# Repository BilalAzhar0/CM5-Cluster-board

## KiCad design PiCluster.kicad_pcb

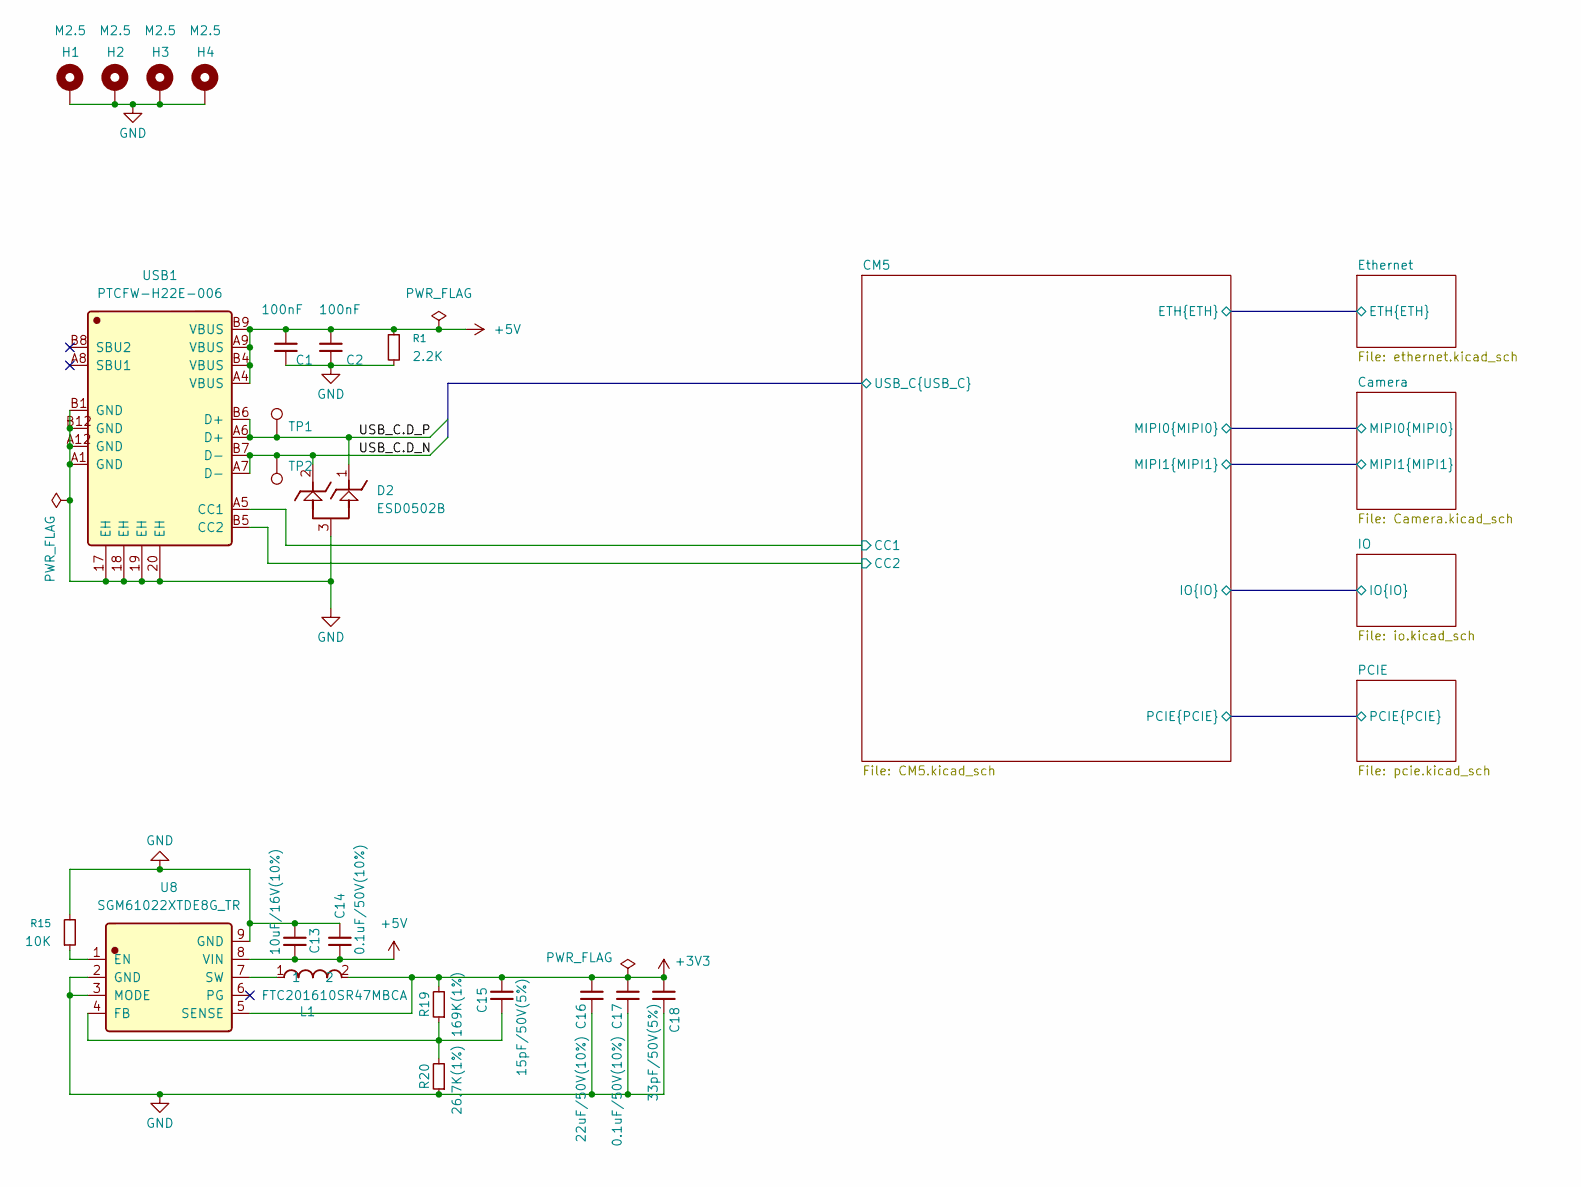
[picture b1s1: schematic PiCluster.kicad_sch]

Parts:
C1, C2: 100nF; C_0402_1005Metric
C13: 10uF/16V(10%); C_0603_1608Metric
C14, C17: 0.1uF/50V(10%); C_0402_1005Metric
C15: 15pF/50V(5%); C_0402_1005Metric
C16: 22uF/50V(10%); C_0603_1608Metric
C18: 33pF/50V(5%); C_0402_1005Metric
D2: ESD0502B; Manufacturer Part ESD0502B-HXY; LCSC C4748781
H1, H2, H3, H4: M2.5; MountingHole_2.5mm_Pad_TopBottom
L1: FTC201610SR47MBCA; Manufacturer Part FTC201610SR47MBCA; LCSC C5832340
R1: 2.2K; R_0402_1005Metric
R15: 10K; R_0402_1005Metric
R19: 169K(1%); R_0402_1005Metric
R20: 26.7K(1%); R_0402_1005Metric
TP1, TP2: TestPoint; TestPoint_Pad_D1.0mm
U8: SGM61022XTDE8G_TR; Manufacturer Part SGM61022XTDE8G/TR; LCSC C5153652
USB1: PTCFW-H22E-006; Manufacturer Part PTCFW-H22E-006; LCSC C54829830

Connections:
+3V3: C15.2, C16.2, C17.2, C18.2, L1.2, R19.2, U8.5 (SENSE); also elsewhere on the board
+5V: C1.1, C2.1, C13.1, C14.2, R1.1, U8.8 (VIN), USB1.A4 (VBUS), USB1.A9 (VBUS), USB1.B4 (VBUS), USB1.B9 (VBUS); also elsewhere on the board
/CM5/CC1: USB1.A5 (CC1); also elsewhere on the board
/CM5/CC2: USB1.B5 (CC2); also elsewhere on the board
/CM5/USB_C.D_N: D2.2, TP2.1 (1_1), USB1.A7 (D-), USB1.B7 (D-); also elsewhere on the board
/CM5/USB_C.D_P: D2.1, TP1.1 (1_1), USB1.A6 (D+), USB1.B6 (D+); also elsewhere on the board
GND: C1.2, C2.2, C13.2, C14.1, C16.1, C17.1, C18.1, D2.3, H1.1 (1_1), H2.1 (1_1), H3.1 (1_1), H4.1 (1_1), R1.2, R15.2, R20.1, U8.2 (GND), U8.3 (MODE), U8.9 (GND), USB1.17 (EH), USB1.18 (EH), USB1.19 (EH), USB1.20 (EH), USB1.A1 (GND), USB1.A12 (GND), USB1.B1 (GND), USB1.B12 (GND); also elsewhere on the board
unnamed: R15.1, U8.1 (EN)
unnamed: C15.1, R19.1, R20.2, U8.4 (FB)
unnamed: L1.1, U8.7 (SW)

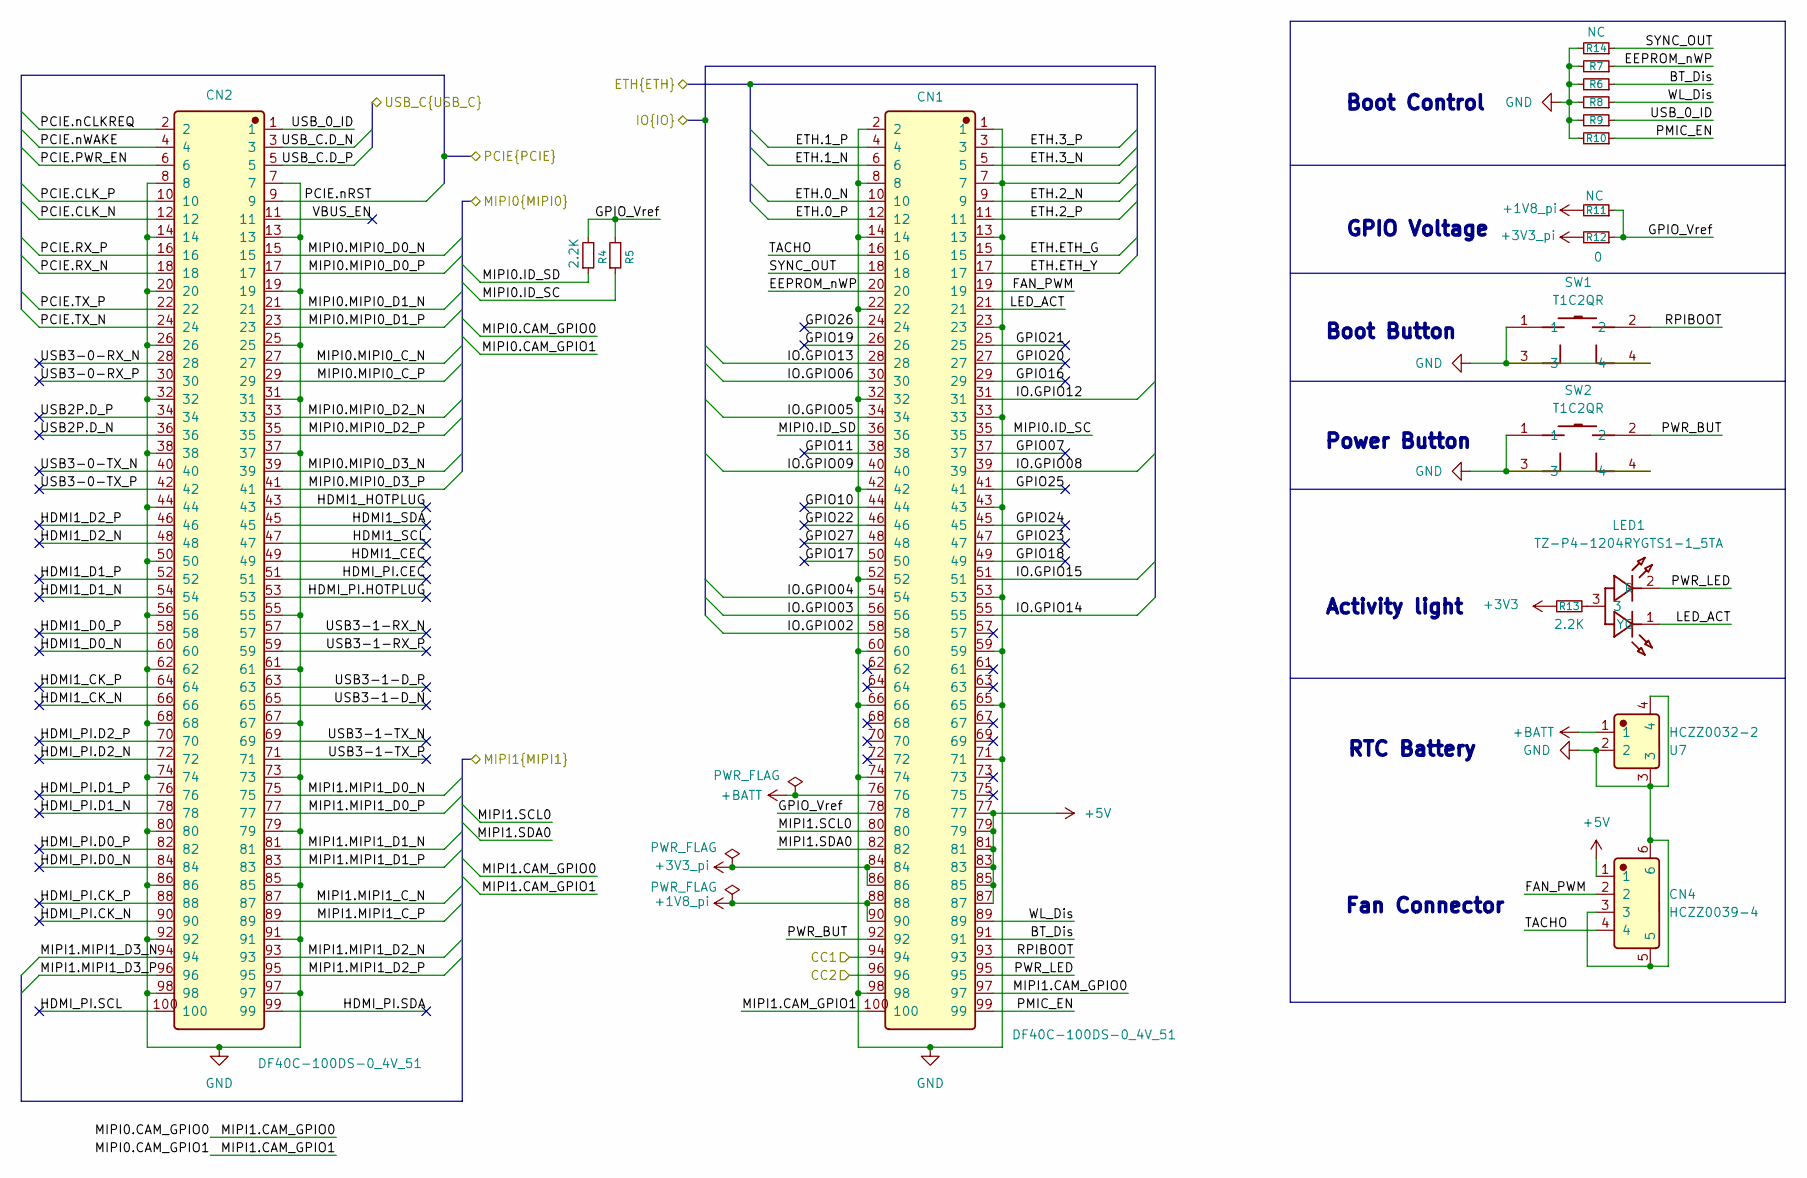
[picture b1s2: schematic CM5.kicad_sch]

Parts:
CN1, CN2: DF40C-100DS-0_4V_51; Manufacturer Part DF40C-100DS-0.4V(51); LCSC C597931
CN4: HCZZ0039-4; Manufacturer Part HCZZ0039-4; LCSC C7433440
LED1: TZ-P4-1204RYGTS1-1_5TA; Manufacturer Part TZ-P4-1204RYGTS1-1.5TA; LCSC C916079
R4, R5, R13: 2.2K; R_0402_1005Metric
R6, R7, R8, R9, R10, R11, R14: NC; R_0402_1005Metric
R12: 0; R_0402_1005Metric
SW1, SW2: T1C2QR; Manufacturer Part T1C2QR; LCSC C495948
U7: HCZZ0032-2; Manufacturer Part HCZZ0032-2; LCSC C7433423

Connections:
+1V8_pi: CN1.88, CN1.90, R11.2
+3V3: R13.1; also elsewhere on the board
+3V3_pi: CN1.84, CN1.86, R12.2
+5V: CN1.77, CN1.79, CN1.81, CN1.83, CN1.85, CN1.87, CN4.1; also elsewhere on the board
+BATT: CN1.76, U7.1
/CM5/BT_Dis: CN1.91, R6.1
/CM5/CC1: CN1.94; also elsewhere on the board
/CM5/CC2: CN1.96; also elsewhere on the board
/CM5/EEPROM_nWP: CN1.20, R7.1
/CM5/ETH.0_N: CN1.10; also elsewhere on the board
/CM5/ETH.0_P: CN1.12; also elsewhere on the board
/CM5/ETH.1_N: CN1.6; also elsewhere on the board
/CM5/ETH.1_P: CN1.4; also elsewhere on the board
/CM5/ETH.2_N: CN1.9; also elsewhere on the board
/CM5/ETH.2_P: CN1.11; also elsewhere on the board
/CM5/ETH.3_N: CN1.5; also elsewhere on the board
/CM5/ETH.3_P: CN1.3; also elsewhere on the board
/CM5/ETH.ETH_G: CN1.15; also elsewhere on the board
/CM5/ETH.ETH_Y: CN1.17; also elsewhere on the board
/CM5/FAN_PWM: CN1.19, CN4.2
/CM5/GPIO07: CN1.37
/CM5/GPIO10: CN1.44
/CM5/GPIO11: CN1.38
/CM5/GPIO16: CN1.29
/CM5/GPIO17: CN1.50
/CM5/GPIO18: CN1.49
/CM5/GPIO19: CN1.26
/CM5/GPIO20: CN1.27
/CM5/GPIO21: CN1.25
/CM5/GPIO22: CN1.46
/CM5/GPIO23: CN1.47
/CM5/GPIO24: CN1.45
/CM5/GPIO25: CN1.41
/CM5/GPIO26: CN1.24
/CM5/GPIO27: CN1.48
/CM5/GPIO_Vref: CN1.78, R4.2, R5.2, R11.1, R12.1
/CM5/HDMI1_CEC: CN2.49
/CM5/HDMI1_CK_N: CN2.66
/CM5/HDMI1_CK_P: CN2.64
/CM5/HDMI1_D0_N: CN2.60
/CM5/HDMI1_D0_P: CN2.58
/CM5/HDMI1_D1_N: CN2.54
/CM5/HDMI1_D1_P: CN2.52
/CM5/HDMI1_D2_N: CN2.48
/CM5/HDMI1_D2_P: CN2.46
/CM5/HDMI1_HOTPLUG: CN2.43
/CM5/HDMI1_SCL: CN2.47
/CM5/HDMI1_SDA: CN2.45
/CM5/HDMI_PI.CEC: CN2.51
/CM5/HDMI_PI.CK_N: CN2.90
/CM5/HDMI_PI.CK_P: CN2.88
/CM5/HDMI_PI.D0_N: CN2.84
/CM5/HDMI_PI.D0_P: CN2.82
/CM5/HDMI_PI.D1_N: CN2.78
/CM5/HDMI_PI.D1_P: CN2.76
/CM5/HDMI_PI.D2_N: CN2.72
/CM5/HDMI_PI.D2_P: CN2.70
/CM5/HDMI_PI.HOTPLUG: CN2.53
/CM5/HDMI_PI.SCL: CN2.100
/CM5/HDMI_PI.SDA: CN2.99
/CM5/IO.GPIO02: CN1.58; also elsewhere on the board
/CM5/IO.GPIO03: CN1.56; also elsewhere on the board
/CM5/IO.GPIO04: CN1.54; also elsewhere on the board
/CM5/IO.GPIO05: CN1.34; also elsewhere on the board
/CM5/IO.GPIO06: CN1.30; also elsewhere on the board
/CM5/IO.GPIO08: CN1.39; also elsewhere on the board
/CM5/IO.GPIO09: CN1.40; also elsewhere on the board
/CM5/IO.GPIO12: CN1.31; also elsewhere on the board
/CM5/IO.GPIO13: CN1.28; also elsewhere on the board
/CM5/IO.GPIO14: CN1.55; also elsewhere on the board
/CM5/IO.GPIO15: CN1.51; also elsewhere on the board
/CM5/LED_ACT: CN1.21, LED1.1 (YG)
/CM5/MIPI0.ID_SC: CN1.35, R5.1; also elsewhere on the board
/CM5/MIPI0.ID_SD: CN1.36, R4.1; also elsewhere on the board
/CM5/MIPI0.MIPI0_C_N: CN2.27; also elsewhere on the board
/CM5/MIPI0.MIPI0_C_P: CN2.29; also elsewhere on the board
/CM5/MIPI0.MIPI0_D0_N: CN2.15; also elsewhere on the board
/CM5/MIPI0.MIPI0_D0_P: CN2.17; also elsewhere on the board
/CM5/MIPI0.MIPI0_D1_N: CN2.21; also elsewhere on the board
/CM5/MIPI0.MIPI0_D1_P: CN2.23; also elsewhere on the board
/CM5/MIPI0.MIPI0_D2_N: CN2.33; also elsewhere on the board
/CM5/MIPI0.MIPI0_D2_P: CN2.35; also elsewhere on the board
/CM5/MIPI0.MIPI0_D3_N: CN2.39; also elsewhere on the board
/CM5/MIPI0.MIPI0_D3_P: CN2.41; also elsewhere on the board
/CM5/MIPI1.CAM_GPIO0: CN1.97; also elsewhere on the board
/CM5/MIPI1.CAM_GPIO1: CN1.100; also elsewhere on the board
/CM5/MIPI1.MIPI1_C_N: CN2.87; also elsewhere on the board
/CM5/MIPI1.MIPI1_C_P: CN2.89; also elsewhere on the board
/CM5/MIPI1.MIPI1_D0_N: CN2.75; also elsewhere on the board
/CM5/MIPI1.MIPI1_D0_P: CN2.77; also elsewhere on the board
/CM5/MIPI1.MIPI1_D1_N: CN2.81; also elsewhere on the board
/CM5/MIPI1.MIPI1_D1_P: CN2.83; also elsewhere on the board
/CM5/MIPI1.MIPI1_D2_N: CN2.93; also elsewhere on the board
/CM5/MIPI1.MIPI1_D2_P: CN2.95; also elsewhere on the board
/CM5/MIPI1.MIPI1_D3_N: CN2.94; also elsewhere on the board
/CM5/MIPI1.MIPI1_D3_P: CN2.96; also elsewhere on the board
/CM5/MIPI1.SCL0: CN1.80; also elsewhere on the board
/CM5/MIPI1.SDA0: CN1.82; also elsewhere on the board
/CM5/PCIE.CLK_N: CN2.12; also elsewhere on the board
/CM5/PCIE.CLK_P: CN2.10; also elsewhere on the board
/CM5/PCIE.PWR_EN: CN2.6; also elsewhere on the board
/CM5/PCIE.RX_N: CN2.18; also elsewhere on the board
/CM5/PCIE.RX_P: CN2.16; also elsewhere on the board
/CM5/PCIE.TX_N: CN2.24; also elsewhere on the board
/CM5/PCIE.TX_P: CN2.22; also elsewhere on the board
/CM5/PCIE.nCLKREQ: CN2.2; also elsewhere on the board
/CM5/PCIE.nRST: CN2.9; also elsewhere on the board
/CM5/PCIE.nWAKE: CN2.4; also elsewhere on the board
/CM5/PMIC_EN: CN1.99, R10.1
/CM5/PWR_BUT: CN1.92, SW2.2
/CM5/PWR_LED: CN1.95, LED1.2 (R)
/CM5/RPIBOOT: CN1.93, SW1.2
/CM5/SYNC_OUT: CN1.18, R14.1
/CM5/TACHO: CN1.16, CN4.4
/CM5/USB2P.D_N: CN2.36
/CM5/USB2P.D_P: CN2.34
/CM5/USB3-0-RX_N: CN2.28
/CM5/USB3-0-RX_P: CN2.30
/CM5/USB3-0-TX_N: CN2.40
/CM5/USB3-0-TX_P: CN2.42
/CM5/USB3-1-D_N: CN2.65
/CM5/USB3-1-D_P: CN2.63
/CM5/USB3-1-RX_N: CN2.57
/CM5/USB3-1-RX_P: CN2.59
/CM5/USB3-1-TX_N: CN2.69
/CM5/USB3-1-TX_P: CN2.71
/CM5/USB_0_ID: CN2.1, R9.1
/CM5/USB_C.D_N: CN2.3; also elsewhere on the board
/CM5/USB_C.D_P: CN2.5; also elsewhere on the board
/CM5/VBUS_EN: CN2.11
/CM5/WL_Dis: CN1.89, R8.1
GND: CN1.1, CN1.2, CN1.7, CN1.8, CN1.13, CN1.14, CN1.22, CN1.23, CN1.32, CN1.33, CN1.42, CN1.43, CN1.52, CN1.53, CN1.59, CN1.60, CN1.65, CN1.66, CN1.71, CN1.74, CN1.98, CN2.7, CN2.8, CN2.13, CN2.14, CN2.19, CN2.20, CN2.25, CN2.26, CN2.31, CN2.32, CN2.37, CN2.38, CN2.44, CN2.50, CN2.55, CN2.56, CN2.61, CN2.62, CN2.67, CN2.68, CN2.73, CN2.74, CN2.79, CN2.80, CN2.85, CN2.86, CN2.91, CN2.92, CN2.97, CN2.98, CN4.3, CN4.5, CN4.6, R6.2, R7.2, R8.2, R9.2, R10.2, R14.2, SW1.1, SW1.3, SW1.4, SW2.1, SW2.3, SW2.4, U7.2, U7.3, U7.4; also elsewhere on the board
unnamed: LED1.3, R13.2

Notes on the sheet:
RTC Battery
Boot Control
GPIO Voltage
Power Button
Activity light
Boot Button
Fan Connector

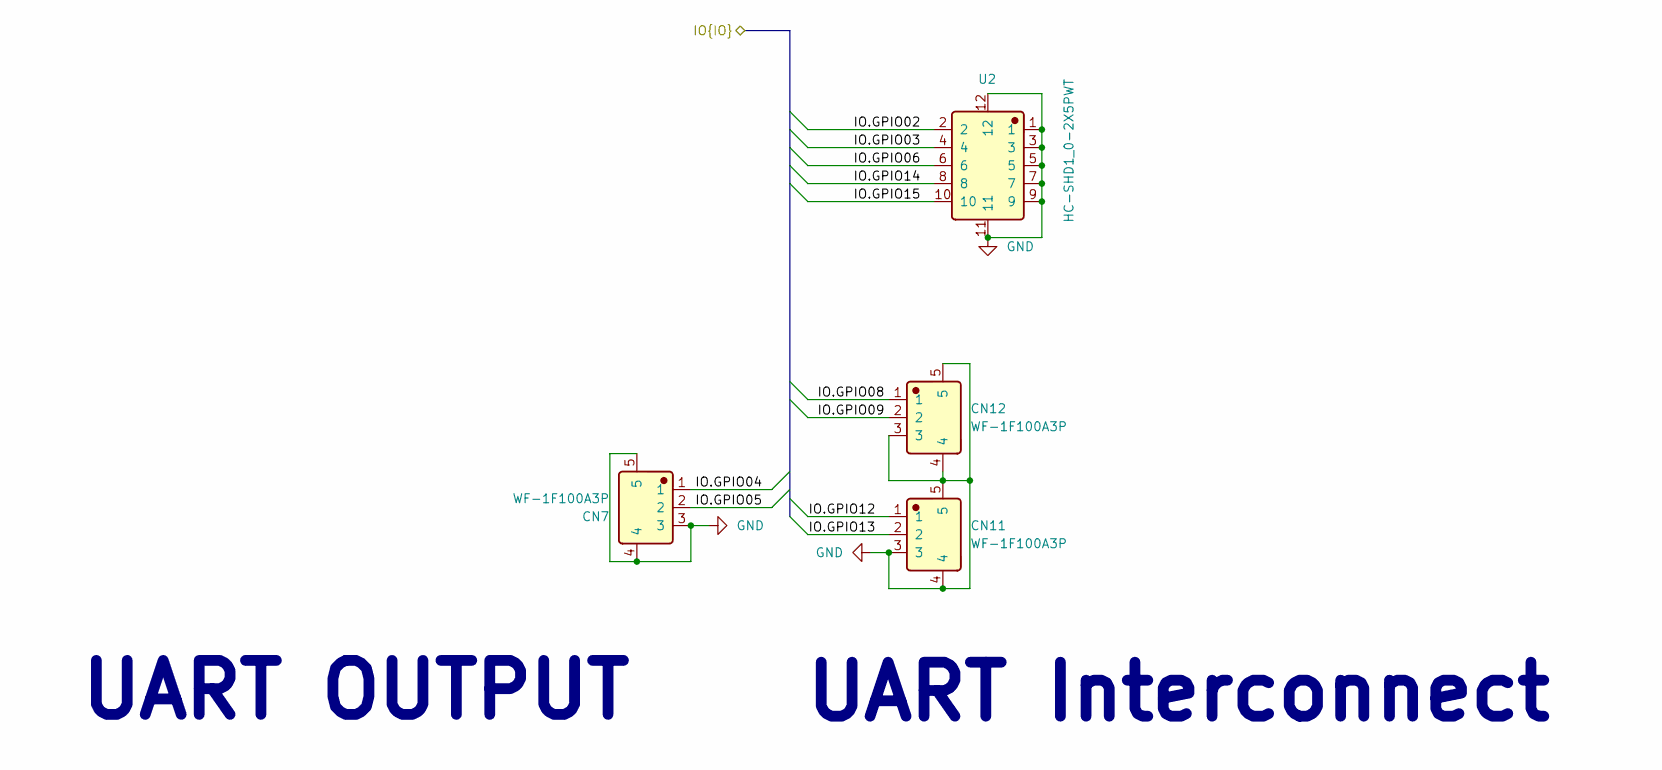
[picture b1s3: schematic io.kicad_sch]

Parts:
CN7, CN11, CN12: WF-1F100A3P; Manufacturer Part WF-1F100A3P; LCSC C23390336
U2: HC-SHD1_0-2X5PWT; Manufacturer Part HC-SHD1.0-2x5PWT; LCSC C19273832

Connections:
/CM5/IO.GPIO02: U2.2; also elsewhere on the board
/CM5/IO.GPIO03: U2.4; also elsewhere on the board
/CM5/IO.GPIO04: CN7.1; also elsewhere on the board
/CM5/IO.GPIO05: CN7.2; also elsewhere on the board
/CM5/IO.GPIO06: U2.6; also elsewhere on the board
/CM5/IO.GPIO08: CN12.1; also elsewhere on the board
/CM5/IO.GPIO09: CN12.2; also elsewhere on the board
/CM5/IO.GPIO12: CN11.1; also elsewhere on the board
/CM5/IO.GPIO13: CN11.2; also elsewhere on the board
/CM5/IO.GPIO14: U2.8; also elsewhere on the board
/CM5/IO.GPIO15: U2.10; also elsewhere on the board
GND: CN7.3, CN7.4, CN7.5, CN11.3, CN11.4, CN11.5, CN12.3, CN12.4, CN12.5, U2.1, U2.3, U2.5, U2.7, U2.9, U2.11, U2.12; also elsewhere on the board

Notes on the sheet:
UART OUTPUT
UART Interconnect

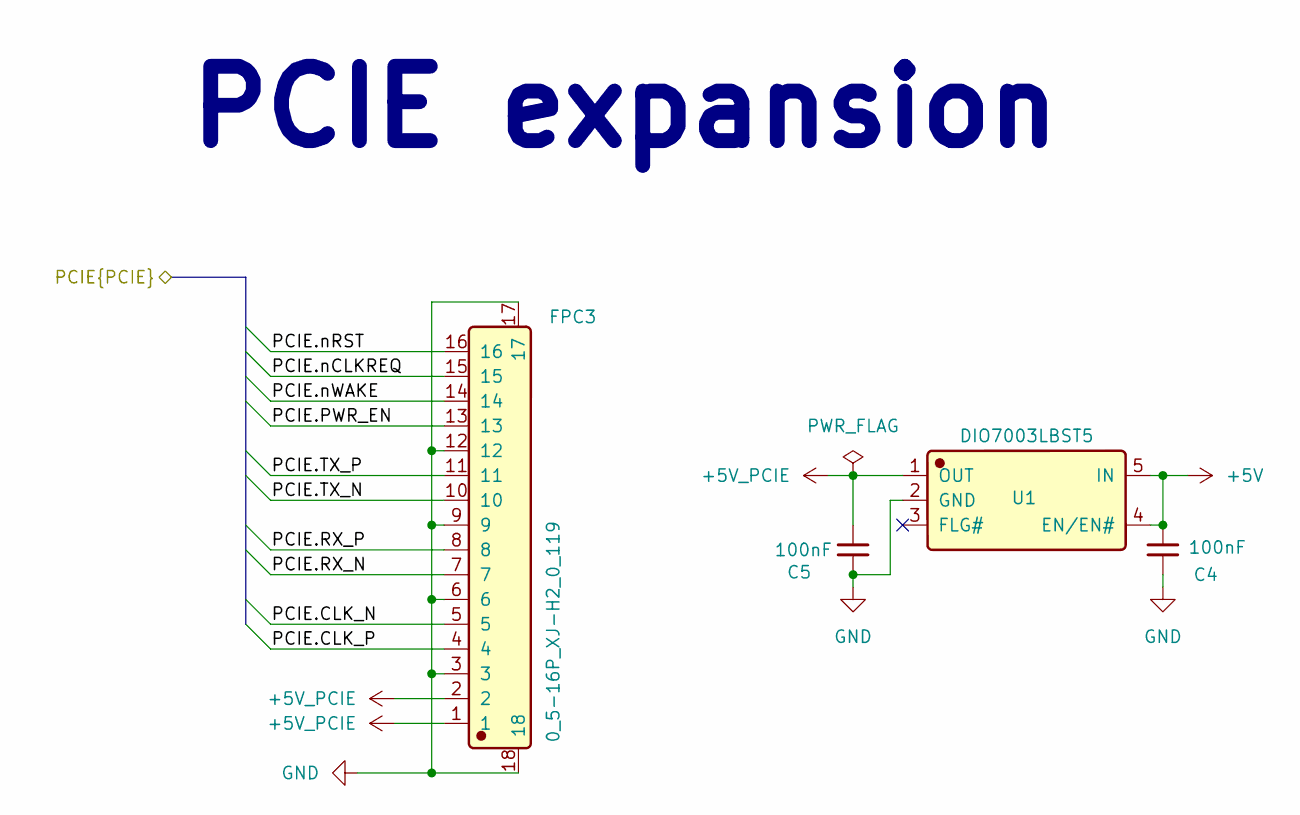
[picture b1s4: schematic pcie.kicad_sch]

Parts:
C4, C5: 100nF; C_0402_1005Metric
FPC3: 0_5-16P_XJ-H2_0_119; Manufacturer Part 0.5-16P XJ-H2.0 119; LCSC C5373436
U1: DIO7003LBST5; Manufacturer Part DIO7003LBST5; LCSC C2920627

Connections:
+5V: C4.1, U1.4 (EN/EN#), U1.5 (IN); also elsewhere on the board
+5V_PCIE: C5.1, FPC3.1, FPC3.2, U1.1 (OUT)
/CM5/PCIE.CLK_N: FPC3.5; also elsewhere on the board
/CM5/PCIE.CLK_P: FPC3.4; also elsewhere on the board
/CM5/PCIE.PWR_EN: FPC3.13; also elsewhere on the board
/CM5/PCIE.RX_N: FPC3.7; also elsewhere on the board
/CM5/PCIE.RX_P: FPC3.8; also elsewhere on the board
/CM5/PCIE.TX_N: FPC3.10; also elsewhere on the board
/CM5/PCIE.TX_P: FPC3.11; also elsewhere on the board
/CM5/PCIE.nCLKREQ: FPC3.15; also elsewhere on the board
/CM5/PCIE.nRST: FPC3.16; also elsewhere on the board
/CM5/PCIE.nWAKE: FPC3.14; also elsewhere on the board
GND: C4.2, C5.2, FPC3.3, FPC3.6, FPC3.9, FPC3.12, FPC3.17, FPC3.18, U1.2 (GND); also elsewhere on the board

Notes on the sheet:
PCIE expansion

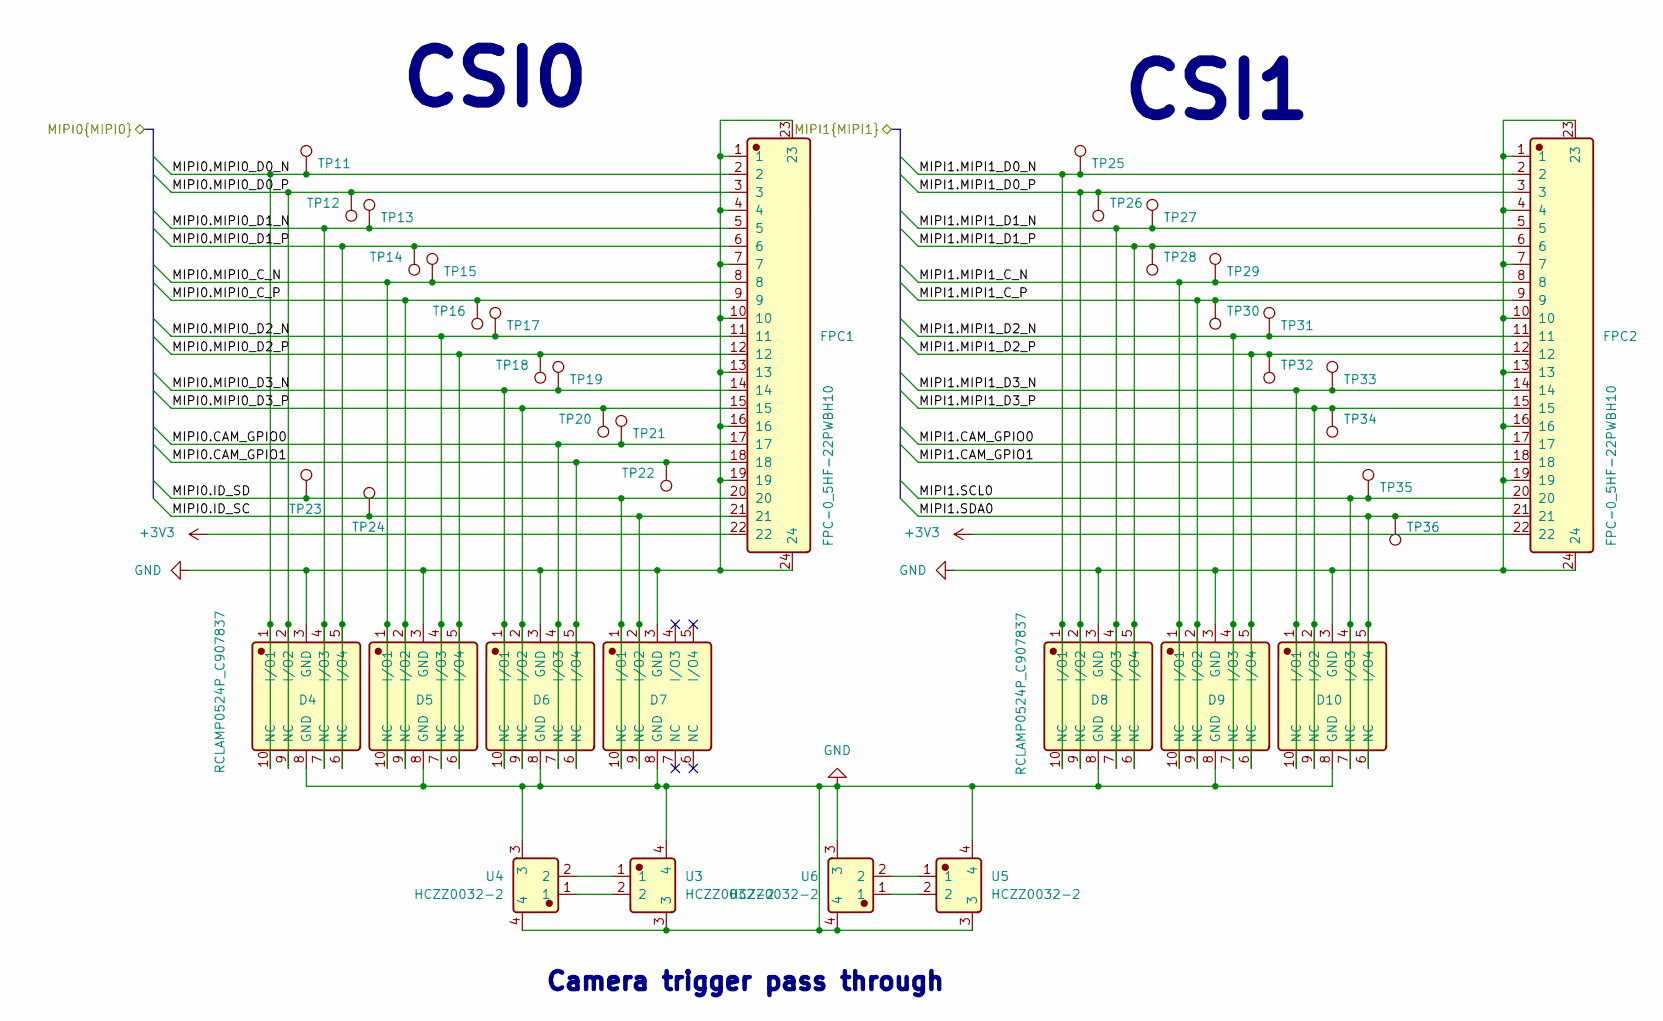
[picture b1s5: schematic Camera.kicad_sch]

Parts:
D4, D5, D6, D7, D8, D9, D10: RCLAMP0524P_C907837; Manufacturer Part RCLAMP0524P; LCSC C907837
FPC1, FPC2: FPC-0_5HF-22PWBH10; Manufacturer Part FPC-0.5HF-22PWBH10; LCSC C5343282
TP11, TP12, TP13, TP14, TP15, TP16, TP17, TP18, TP19, TP20, TP21, TP22, TP23, TP24, TP25, TP26, TP27, TP28, TP29, TP30, TP31, TP32, TP33, TP34, TP35, TP36: TestPoint; TestPoint_Pad_D1.0mm
U3, U4, U5, U6: HCZZ0032-2; Manufacturer Part HCZZ0032-2; LCSC C7433423

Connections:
+3V3: FPC1.22, FPC2.22; also elsewhere on the board
/CM5/MIPI0.ID_SC: D7.2 (I/O2), D7.9 (NC), FPC1.21, TP24.1 (1_1); also elsewhere on the board
/CM5/MIPI0.ID_SD: D7.1 (I/O1), D7.10 (NC), FPC1.20, TP23.1 (1_1); also elsewhere on the board
/CM5/MIPI0.MIPI0_C_N: D5.1 (I/O1), D5.10 (NC), FPC1.8, TP15.1 (1_1); also elsewhere on the board
/CM5/MIPI0.MIPI0_C_P: D5.2 (I/O2), D5.9 (NC), FPC1.9, TP16.1 (1_1); also elsewhere on the board
/CM5/MIPI0.MIPI0_D0_N: D4.1 (I/O1), D4.10 (NC), FPC1.2, TP11.1 (1_1); also elsewhere on the board
/CM5/MIPI0.MIPI0_D0_P: D4.2 (I/O2), D4.9 (NC), FPC1.3, TP12.1 (1_1); also elsewhere on the board
/CM5/MIPI0.MIPI0_D1_N: D4.4 (I/O3), D4.7 (NC), FPC1.5, TP13.1 (1_1); also elsewhere on the board
/CM5/MIPI0.MIPI0_D1_P: D4.5 (I/O4), D4.6 (NC), FPC1.6, TP14.1 (1_1); also elsewhere on the board
/CM5/MIPI0.MIPI0_D2_N: D5.4 (I/O3), D5.7 (NC), FPC1.11, TP17.1 (1_1); also elsewhere on the board
/CM5/MIPI0.MIPI0_D2_P: D5.5 (I/O4), D5.6 (NC), FPC1.12, TP18.1 (1_1); also elsewhere on the board
/CM5/MIPI0.MIPI0_D3_N: D6.1 (I/O1), D6.10 (NC), FPC1.14, TP19.1 (1_1); also elsewhere on the board
/CM5/MIPI0.MIPI0_D3_P: D6.2 (I/O2), D6.9 (NC), FPC1.15, TP20.1 (1_1); also elsewhere on the board
/CM5/MIPI1.CAM_GPIO0: D6.4 (I/O3), D6.7 (NC), FPC1.17, FPC2.17, TP21.1 (1_1); also elsewhere on the board
/CM5/MIPI1.CAM_GPIO1: D6.5 (I/O4), D6.6 (NC), FPC1.18, FPC2.18, TP22.1 (1_1); also elsewhere on the board
/CM5/MIPI1.MIPI1_C_N: D9.1 (I/O1), D9.10 (NC), FPC2.8, TP29.1 (1_1); also elsewhere on the board
/CM5/MIPI1.MIPI1_C_P: D9.2 (I/O2), D9.9 (NC), FPC2.9, TP30.1 (1_1); also elsewhere on the board
/CM5/MIPI1.MIPI1_D0_N: D8.1 (I/O1), D8.10 (NC), FPC2.2, TP25.1 (1_1); also elsewhere on the board
/CM5/MIPI1.MIPI1_D0_P: D8.2 (I/O2), D8.9 (NC), FPC2.3, TP26.1 (1_1); also elsewhere on the board
/CM5/MIPI1.MIPI1_D1_N: D8.4 (I/O3), D8.7 (NC), FPC2.5, TP27.1 (1_1); also elsewhere on the board
/CM5/MIPI1.MIPI1_D1_P: D8.5 (I/O4), D8.6 (NC), FPC2.6, TP28.1 (1_1); also elsewhere on the board
/CM5/MIPI1.MIPI1_D2_N: D9.4 (I/O3), D9.7 (NC), FPC2.11, TP31.1 (1_1); also elsewhere on the board
/CM5/MIPI1.MIPI1_D2_P: D9.5 (I/O4), D9.6 (NC), FPC2.12, TP32.1 (1_1); also elsewhere on the board
/CM5/MIPI1.MIPI1_D3_N: D10.1 (I/O1), D10.10 (NC), FPC2.14, TP33.1 (1_1); also elsewhere on the board
/CM5/MIPI1.MIPI1_D3_P: D10.2 (I/O2), D10.9 (NC), FPC2.15, TP34.1 (1_1); also elsewhere on the board
/CM5/MIPI1.SCL0: D10.4 (I/O3), D10.7 (NC), FPC2.20, TP35.1 (1_1); also elsewhere on the board
/CM5/MIPI1.SDA0: D10.5 (I/O4), D10.6 (NC), FPC2.21, TP36.1 (1_1); also elsewhere on the board
GND: D4.3 (GND), D4.8 (GND), D5.3 (GND), D5.8 (GND), D6.3 (GND), D6.8 (GND), D7.3 (GND), D7.8 (GND), D8.3 (GND), D8.8 (GND), D9.3 (GND), D9.8 (GND), D10.3 (GND), D10.8 (GND), FPC1.1, FPC1.4, FPC1.7, FPC1.10, FPC1.13, FPC1.16, FPC1.19, FPC1.23, FPC1.24, FPC2.1, FPC2.4, FPC2.7, FPC2.10, FPC2.13, FPC2.16, FPC2.19, FPC2.23, FPC2.24, U3.3, U3.4, U4.3, U4.4, U5.3, U5.4, U6.3, U6.4; also elsewhere on the board
unnamed: U3.1, U4.2
unnamed: U3.2, U4.1
unnamed: U5.1, U6.2
unnamed: U5.2, U6.1

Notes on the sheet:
Camera trigger pass through
CSI1
CSI0

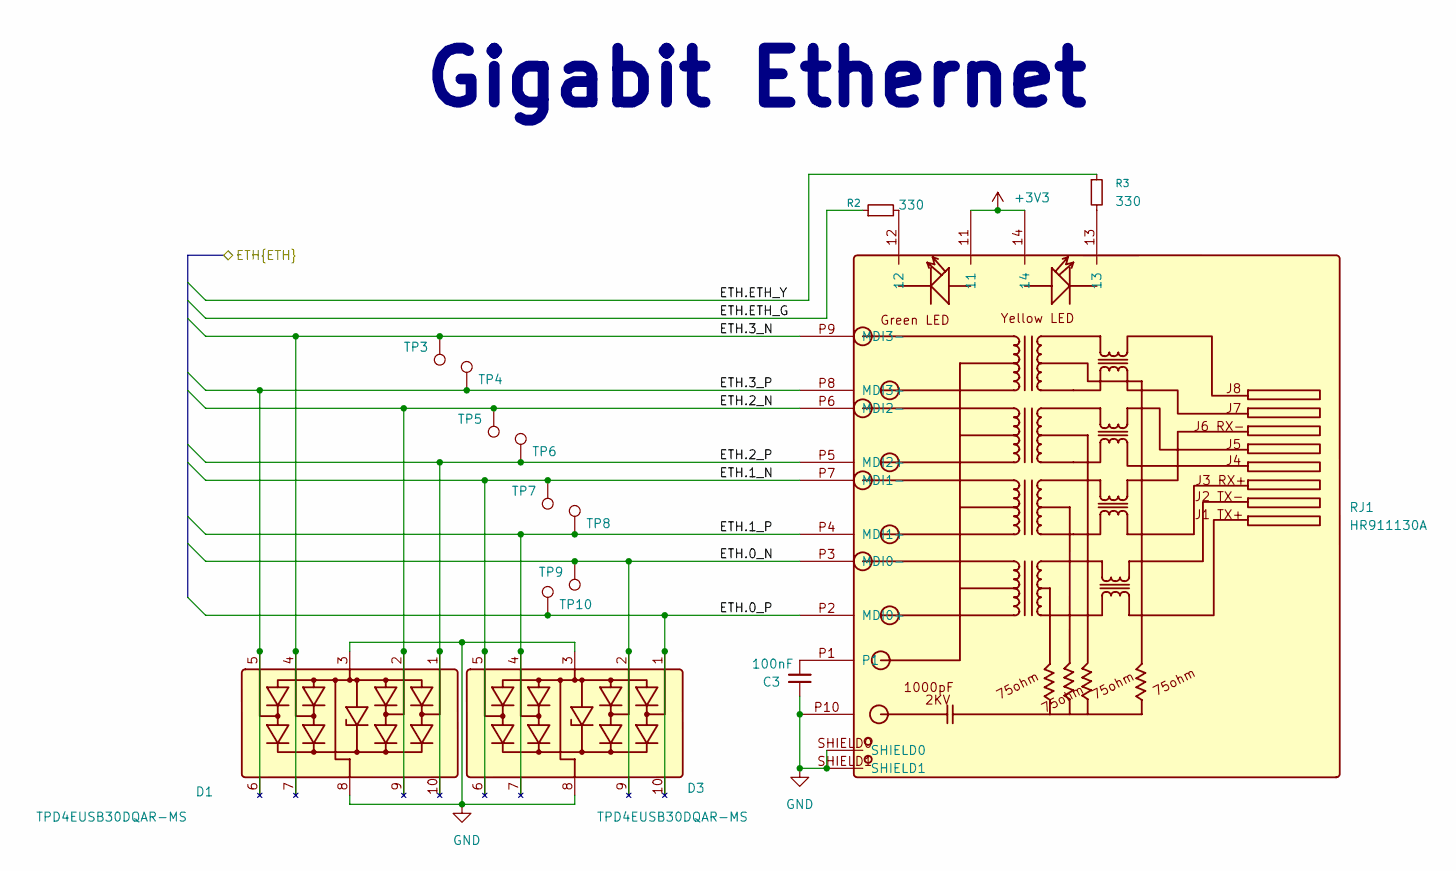
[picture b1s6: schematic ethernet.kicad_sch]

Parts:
C3: 100nF; C_0402_1005Metric
D1, D3: TPD4EUSB30DQAR-MS; Manufacturer Part TPD4EUSB30DQAR-MS; LCSC C6454460
R2, R3: 330; R_0402_1005Metric
RJ1: HR911130A; Manufacturer Part HR911130A; LCSC C54408
TP3, TP4, TP5, TP6, TP7, TP8, TP9, TP10: TestPoint; TestPoint_Pad_D1.0mm

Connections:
+3V3: RJ1.11, RJ1.14; also elsewhere on the board
/CM5/ETH.0_N: D3.2, D3.9, RJ1.P3 (MDI0-), TP9.1 (1_1); also elsewhere on the board
/CM5/ETH.0_P: D3.1, D3.10, RJ1.P2 (MDI0+), TP10.1 (1_1); also elsewhere on the board
/CM5/ETH.1_N: D3.5, D3.6, RJ1.P7 (MDI1-), TP7.1 (1_1); also elsewhere on the board
/CM5/ETH.1_P: D3.4, D3.7, RJ1.P4 (MDI1+), TP8.1 (1_1); also elsewhere on the board
/CM5/ETH.2_N: D1.2, D1.9, RJ1.P6 (MDI2-), TP5.1 (1_1); also elsewhere on the board
/CM5/ETH.2_P: D1.1, D1.10, RJ1.P5 (MDI2+), TP6.1 (1_1); also elsewhere on the board
/CM5/ETH.3_N: D1.4, D1.7, RJ1.P9 (MDI3-), TP3.1 (1_1); also elsewhere on the board
/CM5/ETH.3_P: D1.5, D1.6, RJ1.P8 (MDI3+), TP4.1 (1_1); also elsewhere on the board
/CM5/ETH.ETH_G: R2.1; also elsewhere on the board
/CM5/ETH.ETH_Y: R3.1; also elsewhere on the board
GND: C3.2, D1.3, D1.8, D3.3, D3.8, RJ1.P10, RJ1.SHIELD0, RJ1.SHIELD1; also elsewhere on the board
unnamed: C3.1, RJ1.P1
unnamed: R2.2, RJ1.12
unnamed: R3.2, RJ1.13

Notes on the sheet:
Gigabit Ethernet

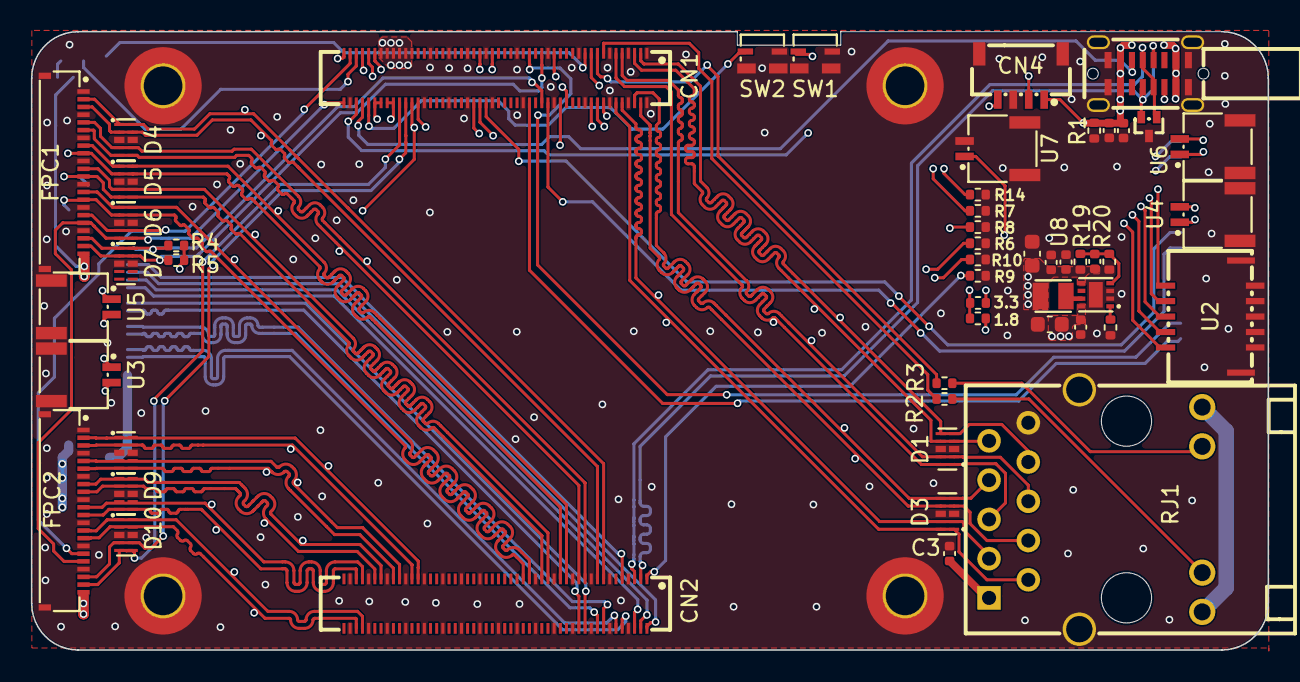
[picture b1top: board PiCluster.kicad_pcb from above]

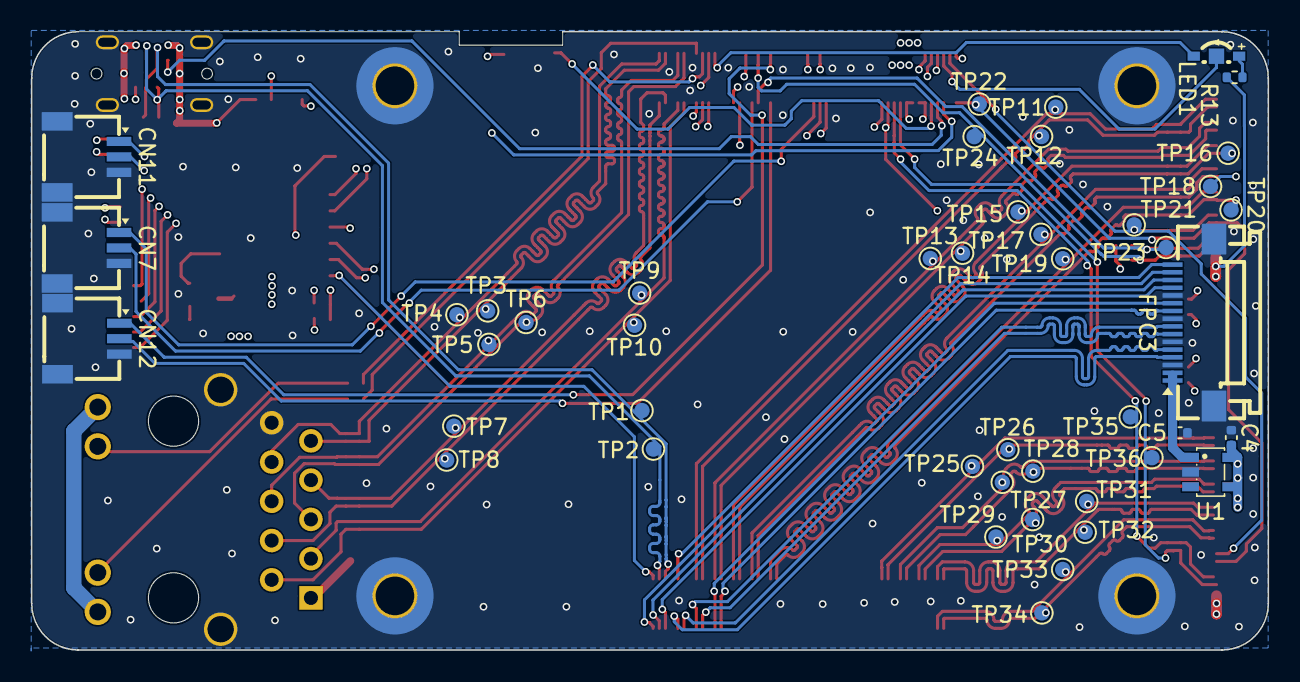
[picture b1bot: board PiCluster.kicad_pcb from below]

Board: 4 copper layers, 80.0 x 40.0 mm, 101 parts (45 on the bottom side), 92 nets.
